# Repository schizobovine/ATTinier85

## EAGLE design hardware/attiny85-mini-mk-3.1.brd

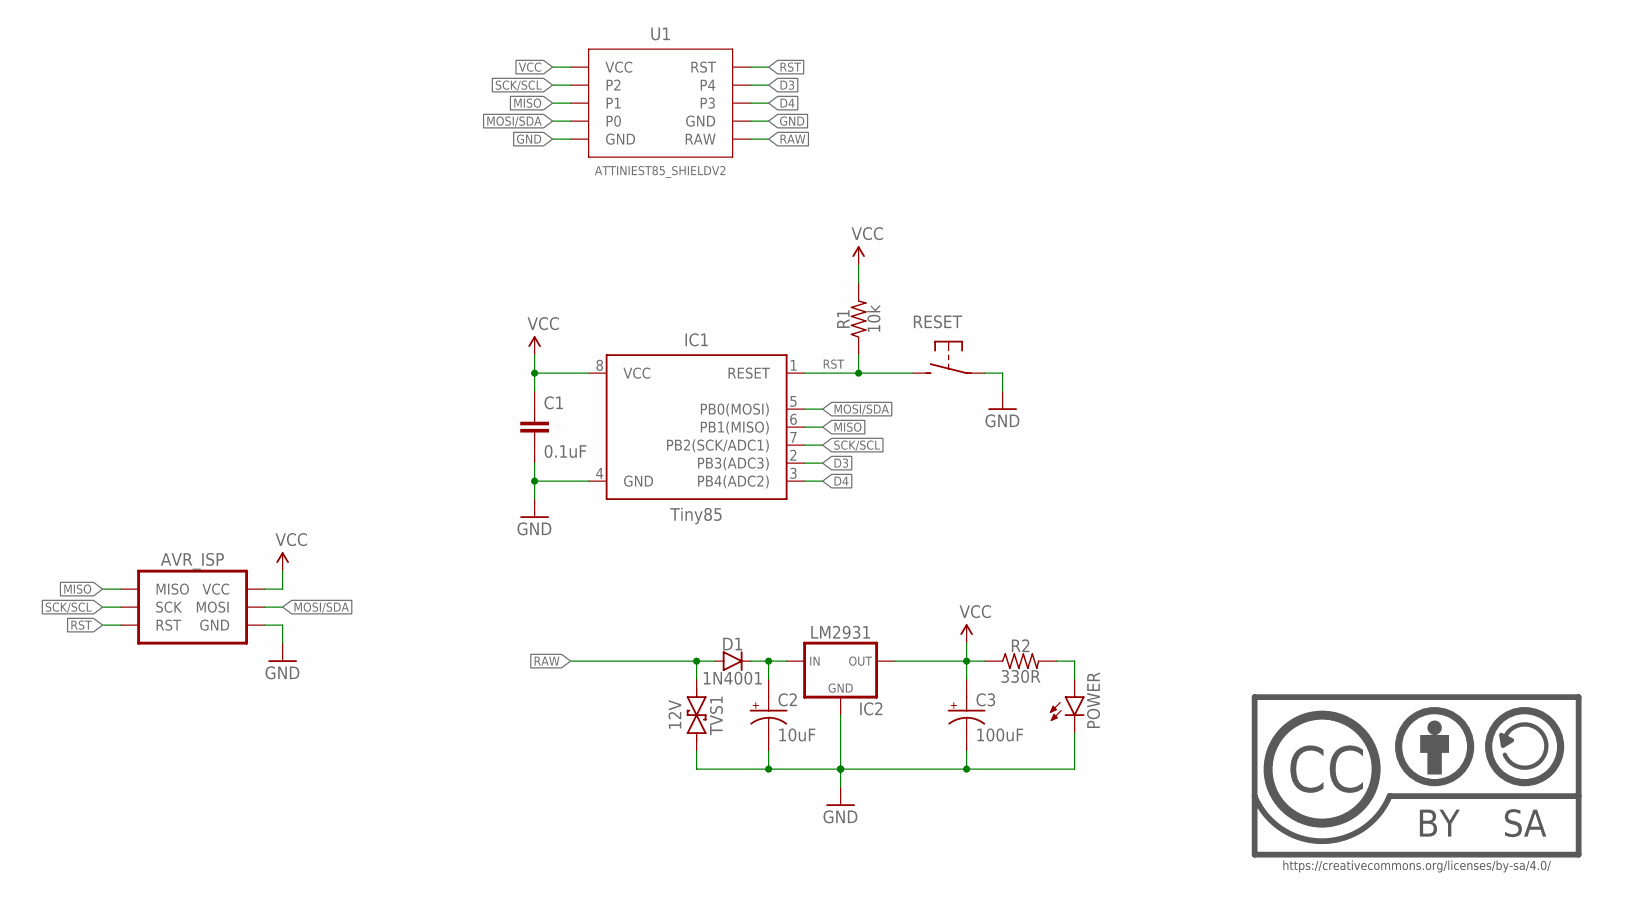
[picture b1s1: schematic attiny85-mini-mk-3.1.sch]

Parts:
AVR_ISP: AVR_SPI_PRG_6PTH; 2X3
C1: 0.1uF; C025-024X044
C2: 10uF; E2,5-5
C3: 100uF; E2,5-5
D1: 1N4001; DIODE-10.16MM
IC1: Tiny85; DIP08
IC2: LM2931; TO-92-AMMO
POWER: LED3MM-LESS; LED3MM-LESSSILK
R1: 10k; RESISTOR-AXIAL-PTH-7.62MM
R2: 330R; RESISTOR-AXIAL-PTH-7.62MM
RESET: DTS-6MM; DTS-3-SMALL-PADS
TVS1: 12V; DO-41-TVS
U1: ATTINIEST85_SHIELDV2; ATTINIEST85_SHIELD_V2
U$1: CC-BY-SA-4.0NO-URL; CC-BY-SA-4.0-NO-URL

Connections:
D3: IC1.2 (PB3(ADC3)), U1.4
D4: IC1.3 (PB4(ADC2)), U1.3
GND: AVR_ISP.6 (GND), C1.2, C2.-, C3.-, IC1.4 (GND), IC2.2 (GND), POWER.K (C), RESET.1, TVS1.P$2 (2), U1.GND@1 (GND), U1.GND@2 (GND)
MISO: AVR_ISP.1 (MISO), IC1.6 (PB1(MISO)), U1.1
MOSI/SDA: AVR_ISP.4 (MOSI), IC1.5 (PB0(MOSI)), U1.0
unnamed: C2.+, D1.C, IC2.1 (IN)
unnamed: POWER.A, R2.P$2 (2)
RAW: D1.A, TVS1.P$1 (1), U1.RAW
RST: AVR_ISP.5 (RST), IC1.1 (RESET), R1.P$1 (1), RESET.2, U1.RST
SCK/SCL: AVR_ISP.3 (SCK), IC1.7 (PB2(SCK/ADC1)), U1.2
VCC: AVR_ISP.2 (VCC), C1.1, C3.+, IC1.8 (VCC), IC2.3 (OUT), R1.P$2 (2), R2.P$1 (1), U1.VCC

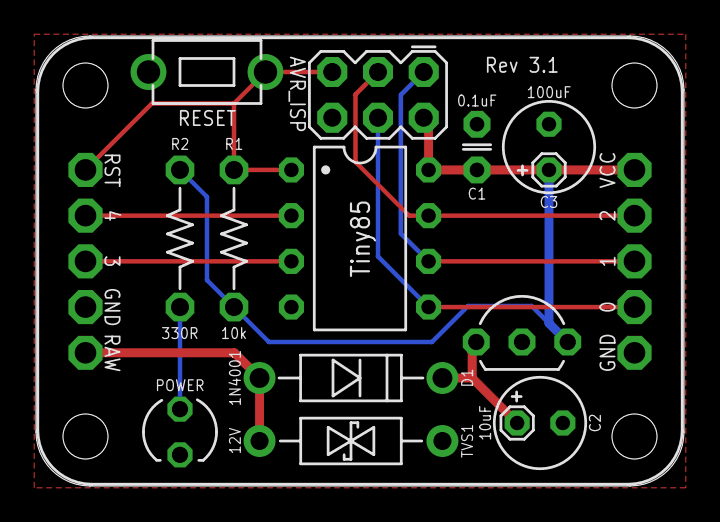
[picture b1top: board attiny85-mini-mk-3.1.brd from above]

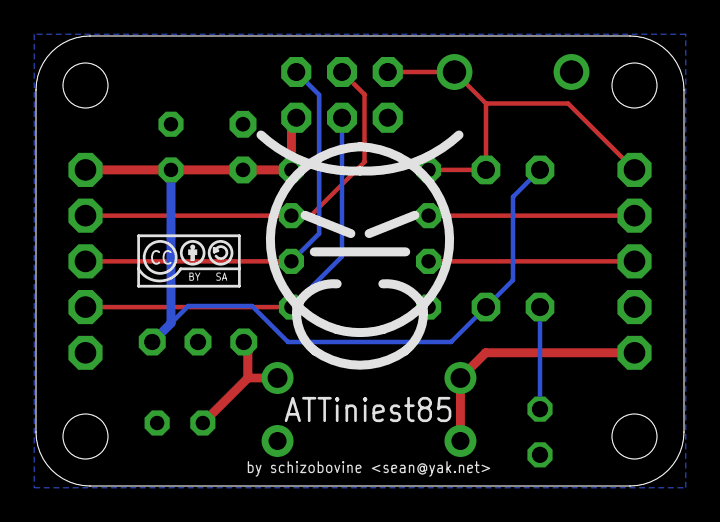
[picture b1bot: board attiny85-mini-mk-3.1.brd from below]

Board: 2 copper layers, 36.0 x 25.0 mm, 15 parts (2 on the bottom side), 11 nets.

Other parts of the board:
U$2: COW

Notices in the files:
parts and their libraries:
A_butts: creativecommons.org/licenses/by-sa/4.0
A_butts: https://creativecommons.org/licenses/by-sa/4.0
